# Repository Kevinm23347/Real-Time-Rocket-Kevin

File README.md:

# Real-Time-Rocket-Kevin
My Work for Rice Eclipse's Real Time Rocket

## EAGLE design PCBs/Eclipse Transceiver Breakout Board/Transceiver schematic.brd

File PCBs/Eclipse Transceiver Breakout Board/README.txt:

Breakout Board for the HOPERF transceiver (RFM95).
Used to test the transceiver without actually placing it onto our main Real Time Rocket Board.
Designed in EAGLE. 
Project File- eagle.epf
Schematic- Transceiver schematic.sch
Board Layout- Transceiver schematic.brd

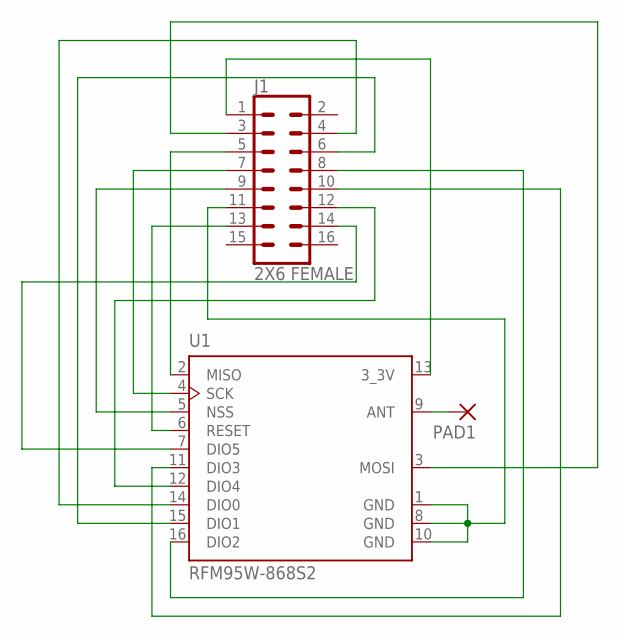
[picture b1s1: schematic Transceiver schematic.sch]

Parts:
J1: 2X6 FEMALE; 2X7
PAD1: 2,54/1,0
U1: RFM95W-868S2; XCVR_RFM95W-868S2

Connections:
unnamed: J1.11, U1.1 (GND), U1.8 (GND), U1.10 (GND)
unnamed: J1.3, U1.3 (MOSI)
unnamed: J1.5, U1.2 (MISO)
unnamed: J1.7, U1.4 (SCK)
unnamed: J1.1, U1.13 (3_3V)
unnamed: J1.4, U1.14 (DIO0)
unnamed: J1.9, U1.5 (NSS)
unnamed: J1.6, U1.15 (DIO1)
unnamed: J1.8, U1.16 (DIO2)
unnamed: J1.10, U1.11 (DIO3)
unnamed: J1.12, U1.12 (DIO4)
unnamed: PAD1.1, U1.9 (ANT)
unnamed: J1.13, U1.6 (RESET)
unnamed: J1.14, U1.7 (DIO5)

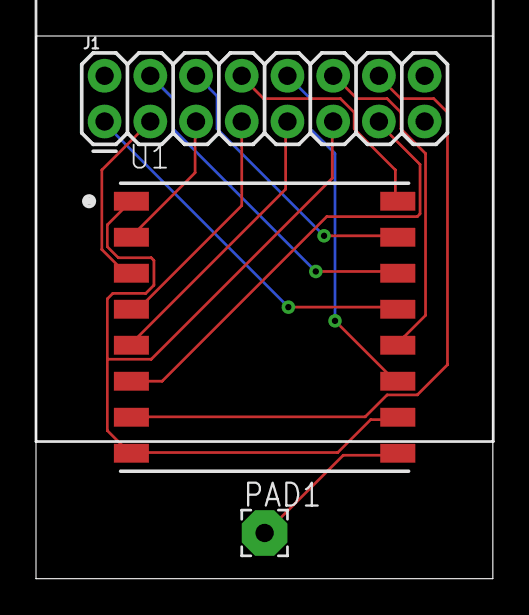
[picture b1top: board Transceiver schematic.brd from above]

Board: 2 copper layers, 25.4 x 30.2 mm, 3 parts (0 on the bottom side), 14 nets.

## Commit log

2019-09-28 Added Transceiver Breakout Board
2019-10-11 Final Update
    This is the design for the board that was milled and used for the RTR testing.
2019-10-11 Create a README
